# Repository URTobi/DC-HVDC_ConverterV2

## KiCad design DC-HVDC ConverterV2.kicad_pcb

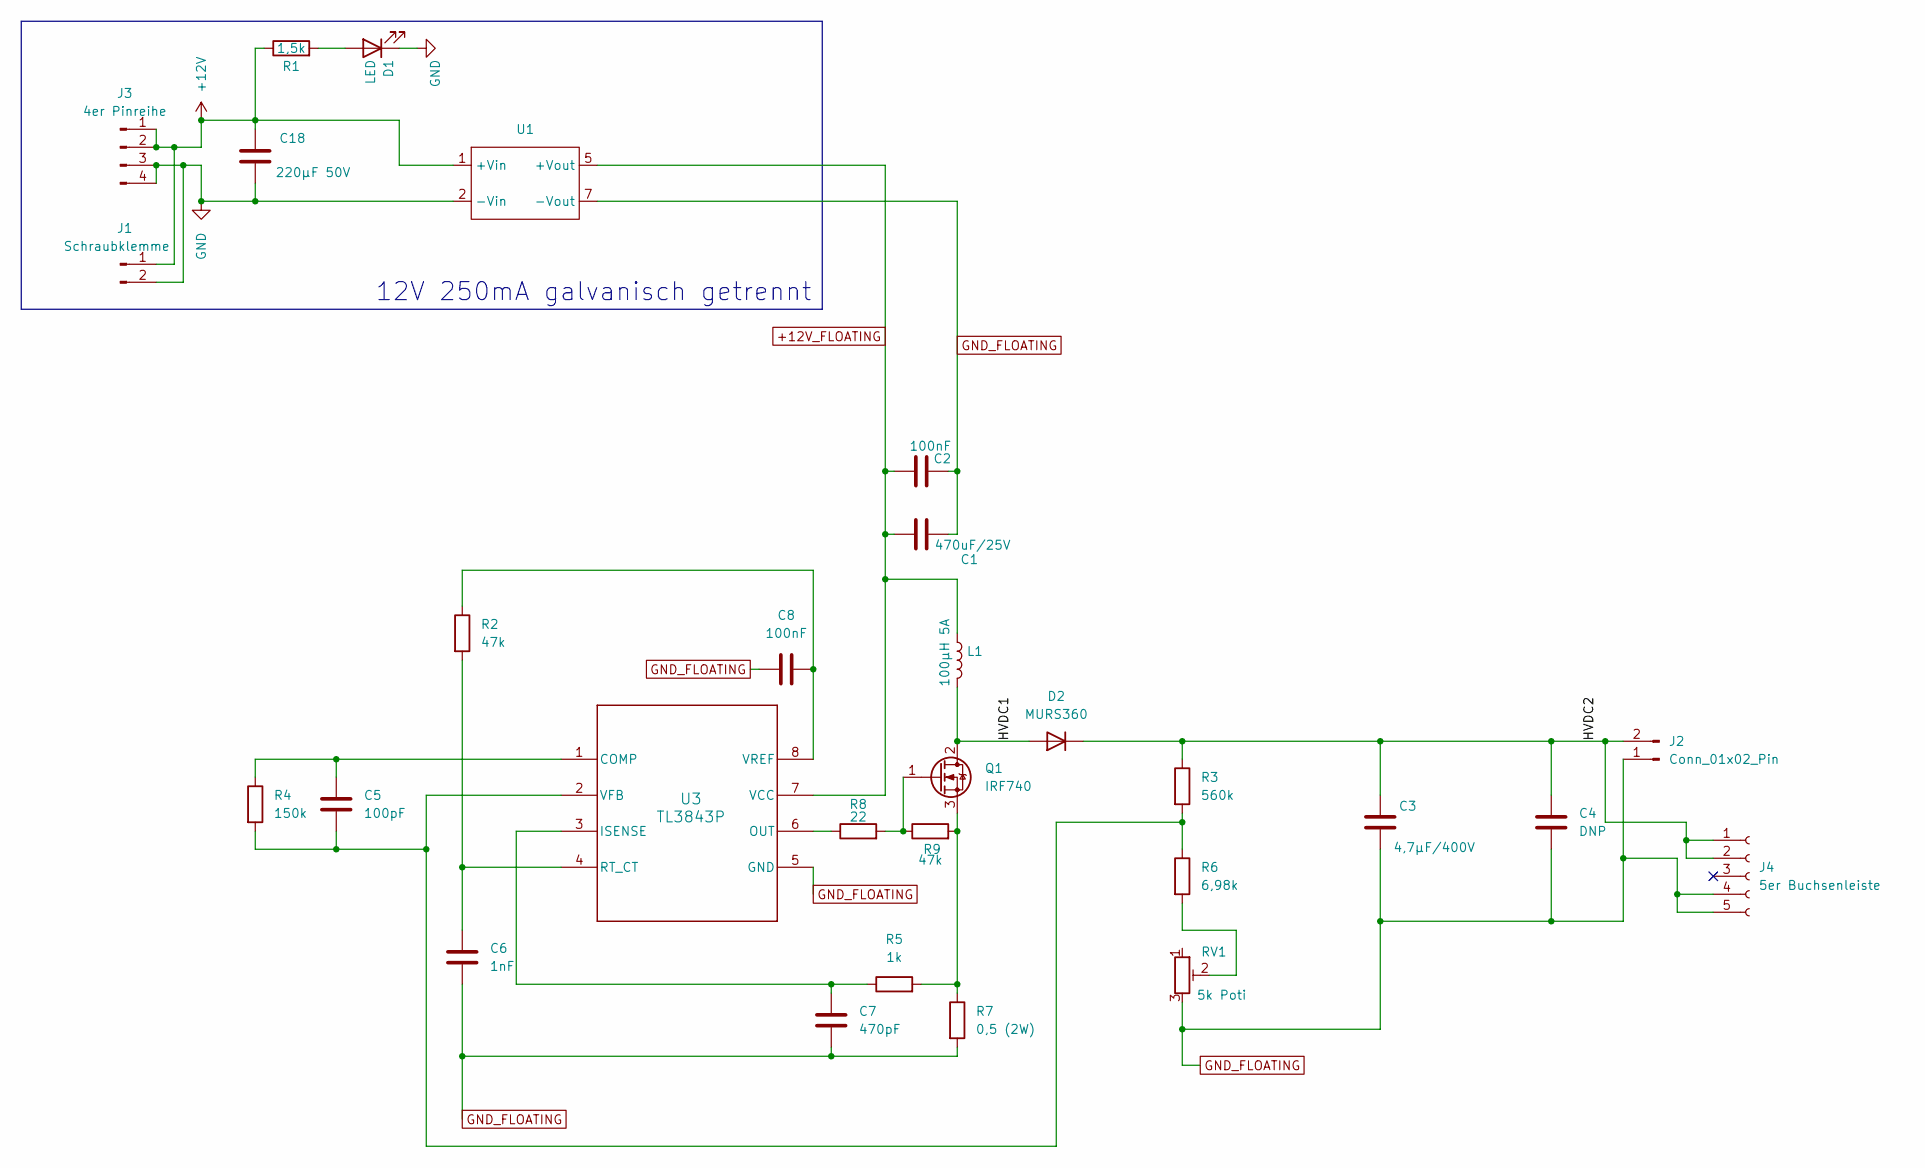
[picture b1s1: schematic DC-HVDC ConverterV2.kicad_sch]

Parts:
C1: 470uF/25V; CP_Radial_D12.5mm_P7.50mm
C2, C8: 100nF; C_0805_2012Metric
C3: 4,7µF/400V; CP_Radial_D14.0mm_P7.50mm
C4: DNP
C5: 100pF; C_0805_2012Metric
C6: 1nF; C_0805_2012Metric
C7: 470pF; C_0805_2012Metric
C18: 220µF 50V; C_Radial_D10.0mm_H16.0mm_P5.00mm
D1: LED; LED_D3.0mm
D2: MURS360; D_SMC_Handsoldering
J1: Schraubklemme; TerminalBlock_MaiXu_MX126-5.0-02P_1x02_P5.00mm
J2: Conn_01x02_Pin; TerminalBlock_MaiXu_MX126-5.0-02P_1x02_P5.00mm
J3: 4er Pinreihe; PinHeader_1x04_P2.54mm_Vertical
J4: 5er Buchsenleiste; PinHeader_1x05_P2.54mm_Vertical
L1: 100µH 5A; L Wuerth 7447070
Q1: IRF740; TO-220-3_Vertical_VERSATZ
R1: 1,5k; R_0805_2012Metric
R2, R9: 47k; R_0805_2012Metric
R3: 560k; R_Axial_DIN0204_L3.6mm_D1.6mm_P7.62mm_Horizontal
R4: 150k; R_0805_2012Metric
R5: 1k; R_0805_2012Metric
R6: 6,98k; R_0805_2012Metric
R7: 0,5 (2W); R_Bare_Metal_Element_L12.4mm_W4.8mm_P11.40mm
R8: 22; R_0805_2012Metric
RV1: 5k Poti; Potentiometer_Bourns_3296W_Vertical
U1: DKB3-12S2PH3
U3: TL3843P; DIP-8_W7.62mm_Socket

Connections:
+12V: C18.1, J1.1, J3.1, J3.2, R1.1, U1.1 (+Vin)
+12V_FLOATING: C1.1, C2.1, L1.1, U1.5 (+Vout), U3.7 (VCC)
/HVDC1: D2.2 (A), L1.2, Q1.2 (D)
/HVDC2: C3.1, C4.1, D2.1 (K), J2.2, J4.1, J4.2, R3.1
GND: C18.2, D1.1 (K), J1.2, J3.3, J3.4, U1.2 (-Vin)
GND_FLOATING: C1.2, C2.2, C3.2, C4.2, C6.2, C7.2, C8.1, J2.1, J4.4, J4.5, R7.2, RV1.3, U1.7 (-Vout), U3.5 (GND)
unnamed: D1.2 (A), R1.2
unnamed: Q1.1 (G), R8.2, R9.1
unnamed: Q1.3 (S), R5.2, R7.1, R9.2
unnamed: R6.2, RV1.2
unnamed: C5.1, R4.1, U3.1 (COMP)
unnamed: C7.1, R5.1, U3.3 (ISENSE)
unnamed: R8.1, U3.6 (OUT)
unnamed: C6.1, R2.2, U3.4 (RT_CT)
unnamed: C5.2, R3.2, R4.2, R6.1, U3.2 (VFB)
unnamed: C8.2, R2.1, U3.8 (VREF)

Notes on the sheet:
12V 250mA galvanisch getrennt

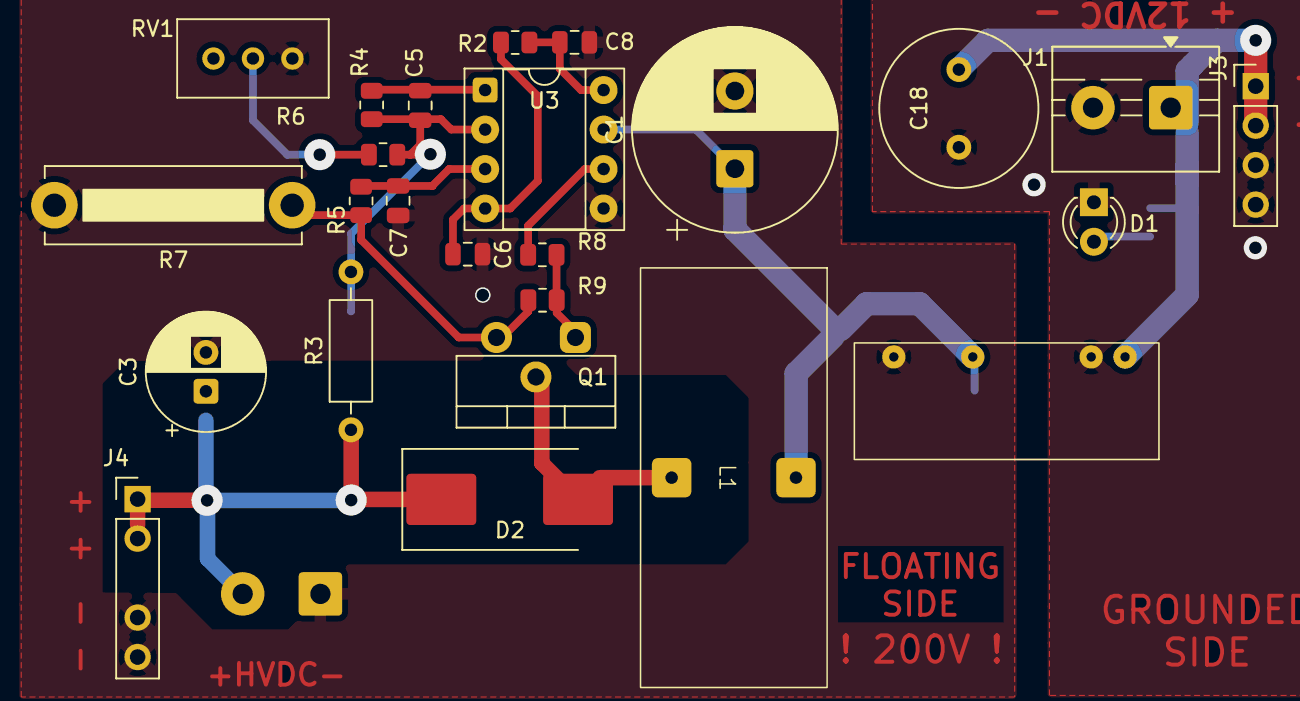
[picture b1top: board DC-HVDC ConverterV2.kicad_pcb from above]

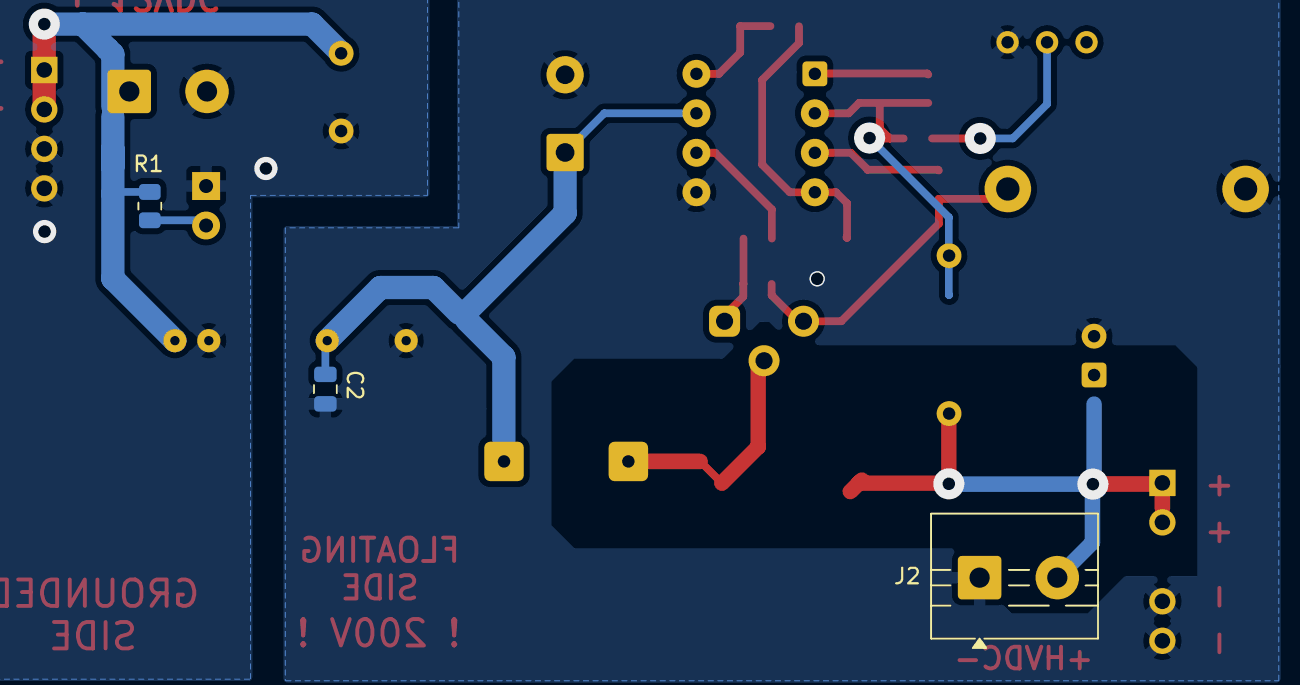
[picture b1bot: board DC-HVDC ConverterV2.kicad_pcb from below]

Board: 2 copper layers, 28 parts (3 on the bottom side), 16 nets.
